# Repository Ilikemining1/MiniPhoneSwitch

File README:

The goal of this project is to build an analog phone switch supporting up to 8 stations and 2 analog trunks.  The switching itself is to be electromechanical in nature, but the control of the switching process and monitoring of lines will be controlled with a microcontroller.  This switch will be designed to be as modular as possible, as with the PCB manufacturing, its common to get multiple boards for your money, making it ideal that many of the boards are identical.

PCB Files are from KiCad, and simulation files are for LTSpice.

Simulation models are property of their respective companies.

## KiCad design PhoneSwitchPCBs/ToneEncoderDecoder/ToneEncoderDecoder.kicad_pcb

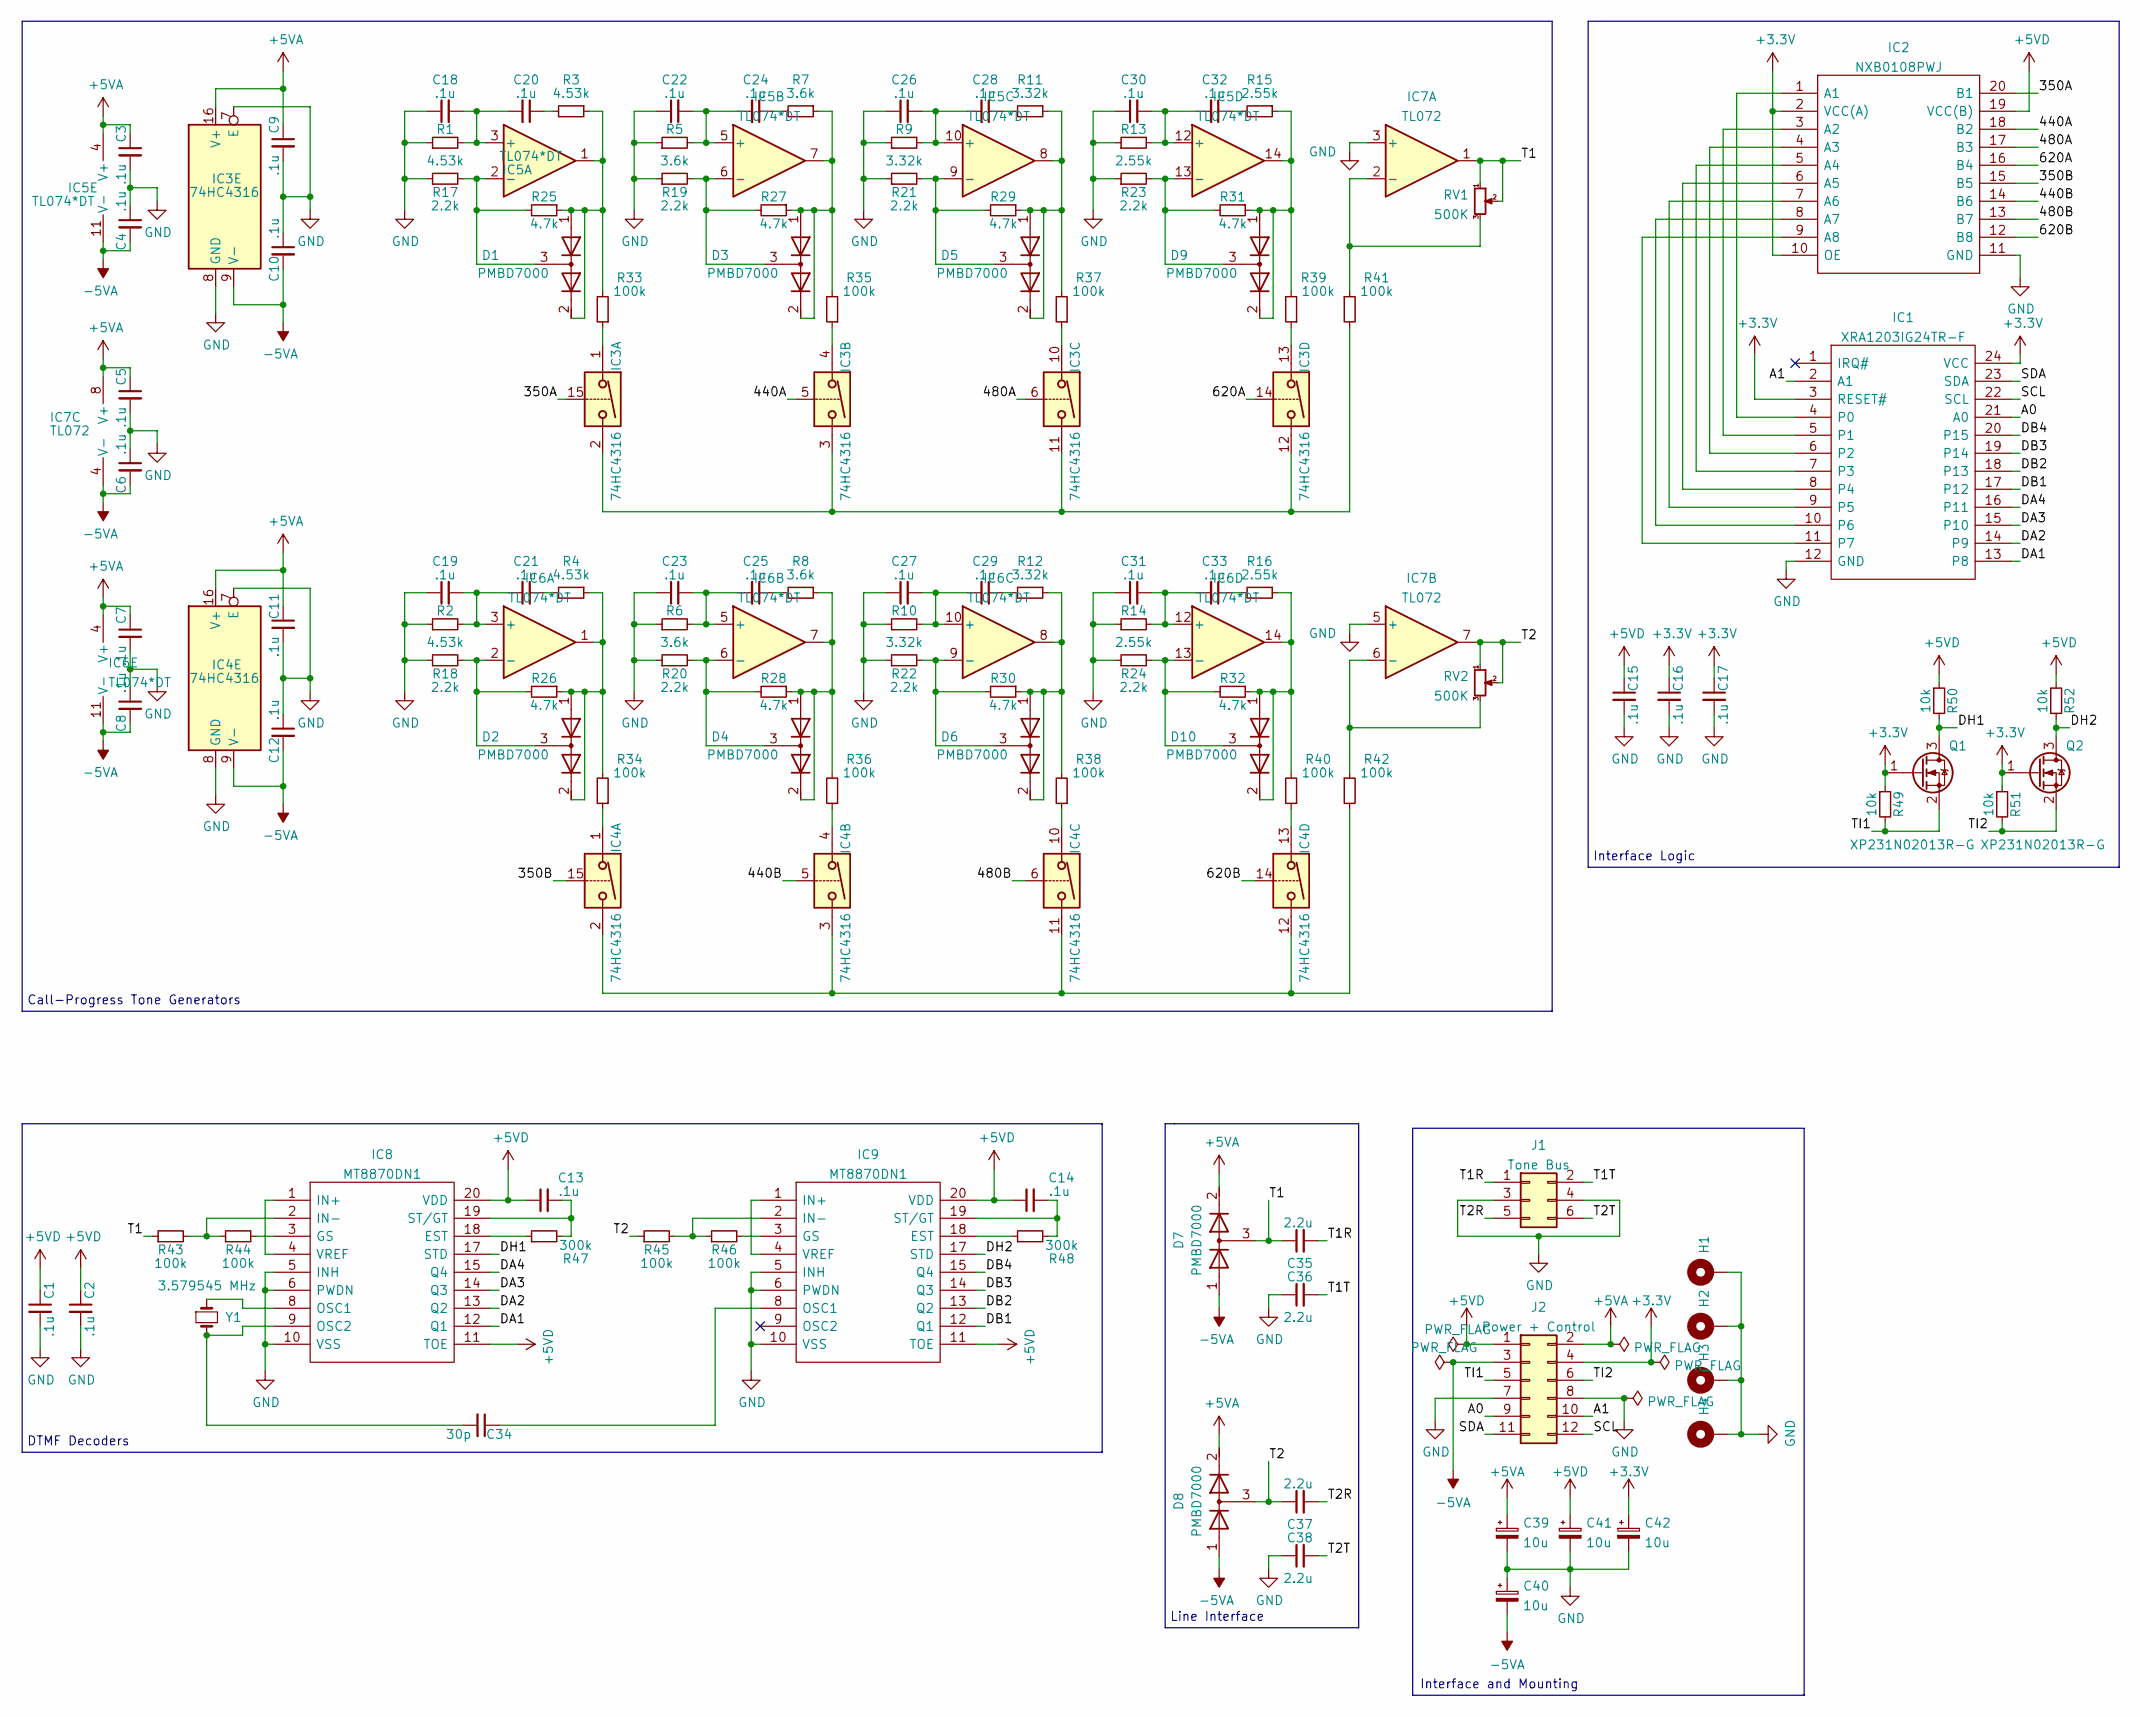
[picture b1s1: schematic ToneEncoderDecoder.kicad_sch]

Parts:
C1, C2, C3, C4, C5, C6, C7, C8, C9, C10, C11, C12, C13, C14, C15, C16, C17: .1u; C_0603_1608Metric_Pad1.08x0.95mm_HandSolder
C18, C19, C20, C21, C22, C23, C24, C25, C26, C27, C28, C29, C30, C31, C32, C33: .1u; C_1206_3216Metric_Pad1.33x1.80mm_HandSolder
C34: 30p; C_0603_1608Metric_Pad1.08x0.95mm_HandSolder
C35, C36, C37, C38: 2.2u; C_Radial_D5.0mm_H11.0mm_P2.00mm
C39, C40, C41, C42: 10u; C_0805_2012Metric_Pad1.18x1.45mm_HandSolder
D1, D2, D3, D4, D5, D6, D7, D8, D9, D10: PMBD7000; SOT-23
H1, H2, H3, H4: M3; MountingHole_3.2mm_M3_Pad
IC1: XRA1203IG24TR-F; TSSOP-24_4.4x7.8mm_P0.65mm
IC2: NXB0108PWJ; TSSOP-20_4.4x6.5mm_P0.65mm
IC3, IC4: 74HC4316; TSSOP-16_4.4x5mm_P0.65mm
IC5, IC6: TL074*DT; SOIC-14_3.9x8.7mm_P1.27mm
IC7: TL072; SOIC-8_3.9x4.9mm_P1.27mm
IC8, IC9: MT8870DN1; SSOP-20_5.3x7.2mm_P0.65mm
J1: Tone Bus; PinHeader_2x03_P2.54mm_Vertical
J2: Power + Control; PinHeader_2x06_P2.54mm_Vertical
Q1, Q2: XP231N02013R-G; SOT-323_SC-70_Handsoldering
R1, R2, R3, R4: 4.53k; R_0603_1608Metric_Pad0.98x0.95mm_HandSolder
R5, R6, R7, R8: 3.6k; R_0603_1608Metric_Pad0.98x0.95mm_HandSolder
R9, R10, R11, R12: 3.32k; R_0603_1608Metric_Pad0.98x0.95mm_HandSolder
R13, R14, R15, R16: 2.55k; R_0603_1608Metric_Pad0.98x0.95mm_HandSolder
R17, R18, R19, R20, R21, R22, R23, R24: 2.2k; R_0603_1608Metric_Pad0.98x0.95mm_HandSolder
R25, R26, R27, R28, R29, R30, R31, R32: 4.7k; R_0603_1608Metric_Pad0.98x0.95mm_HandSolder
R33, R34, R35, R36, R37, R38, R39, R40, R41, R42, R43, R44, R45, R46: 100k; R_0603_1608Metric_Pad0.98x0.95mm_HandSolder
R47, R48: 300k; R_0603_1608Metric_Pad0.98x0.95mm_HandSolder
R49, R50, R51, R52: 10k; R_0603_1608Metric_Pad0.98x0.95mm_HandSolder
RV1, RV2: 500K; Potentiometer_Bourns_3296W_Vertical
Y1: 3.579545 MHz; Crystal_SMD_HC49-SD_HandSoldering

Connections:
+3V3: C16.1, C17.1, C42.1, IC1.3 (RESET#), IC1.24 (VCC), IC2.2 (VCC(A)), IC2.10 (OE), J2.4, Q1.1 (G), Q2.1 (G), R49.1, R51.1
+5VA: C3.1, C5.1, C7.1, C9.1, C11.1, C39.1, D7.2 (K2), D8.2 (K2), IC3.16 (V+), IC4.16 (V+), IC5.4 (V+), IC6.4 (V+), IC7.8 (V+), J2.2
+5VD: C1.1, C2.1, C13.1, C14.1, C15.1, C41.1, IC2.19 (VCC(B)), IC8.11 (TOE), IC8.20 (VDD), IC9.11 (TOE), IC9.20 (VDD), J2.1, R50.1, R52.1
-5VA: C4.2, C6.2, C8.2, C10.2, C12.2, C40.2, D7.1 (A1), D8.1 (A1), IC3.9 (V-), IC4.9 (V-), IC5.11 (V-), IC6.11 (V-), IC7.4 (V-), J2.3
/350A: IC2.20 (B1), IC3.15
/350B: IC2.15 (B5), IC4.15
/440A: IC2.18 (B2), IC3.5
/440B: IC2.14 (B6), IC4.5
/480A: IC2.17 (B3), IC3.6
/480B: IC2.13 (B7), IC4.6
/620A: IC2.16 (B4), IC3.14
/620B: IC2.12 (B8), IC4.14
/A0: IC1.21 (A0), J2.9
/A1: IC1.2 (A1), J2.10
/DA1: IC1.13 (P8), IC8.12 (Q1)
/DA2: IC1.14 (P9), IC8.13 (Q2)
/DA3: IC1.15 (P10), IC8.14 (Q3)
/DA4: IC1.16 (P11), IC8.15 (Q4)
/DB1: IC1.17 (P12), IC9.12 (Q1)
/DB2: IC1.18 (P13), IC9.13 (Q2)
/DB3: IC1.19 (P14), IC9.14 (Q3)
/DB4: IC1.20 (P15), IC9.15 (Q4)
/DH1: IC8.17 (STD), Q1.3 (D), R50.2
/DH2: IC9.17 (STD), Q2.3 (D), R52.2
/SCL: IC1.22 (SCL), J2.12
/SDA: IC1.23 (SDA), J2.11
/T1: C35.1, D7.3 (K1A2), IC7.1, R43.1, RV1.1, RV1.2
/T1R: C35.2, J1.1
/T1T: C36.2, J1.2
/T2: C37.1, D8.3 (K1A2), IC7.7, R45.1, RV2.1, RV2.2
/T2R: C37.2, J1.5
/T2T: C38.2, J1.6
/TI1: J2.5, Q1.2 (S), R49.2
/TI2: J2.6, Q2.2 (S), R51.2
GND: C1.2, C2.2, C3.2, C4.1, C5.2, C6.1, C7.2, C8.1, C9.2, C10.1, C11.2, C12.1, C15.2, C16.2, C17.2, C18.1, C19.1, C22.1, C23.1, C26.1, C27.1, C30.1, C31.1, C36.1, C38.1, C39.2, C40.1, C41.2, C42.2, H1.1, H2.1, H3.1, H4.1, IC1.12 (GND), IC2.11 (GND), IC3.7 (E), IC3.8 (GND), IC4.7 (E), IC4.8 (GND), IC7.3 (+), IC7.5 (+), IC8.5 (INH), IC8.6 (PWDN), IC8.10 (VSS), IC9.5 (INH), IC9.6 (PWDN), IC9.10 (VSS), J1.3, J1.4, J2.7, J2.8, R1.1, R2.1, R5.1, R6.1, R9.1, R10.1, R13.1, R14.1, R17.1, R18.1, R19.1, R20.1, R21.1, R22.1, R23.1, R24.1
unnamed: C13.2, IC8.19 (ST/GT), R47.2
unnamed: C14.2, IC9.19 (ST/GT), R48.2
unnamed: C18.2, C20.2, IC5.3 (+), R1.2
unnamed: C19.2, C21.2, IC6.3 (+), R2.2
unnamed: C20.1, R3.2
unnamed: C21.1, R4.2
unnamed: C22.2, C24.2, IC5.5 (+), R5.2
unnamed: C23.2, C25.2, IC6.5 (+), R6.2
unnamed: C24.1, R7.2
unnamed: C25.1, R8.2
unnamed: C26.2, C28.2, IC5.10 (+), R9.2
unnamed: C27.2, C29.2, IC6.10 (+), R10.2
unnamed: C28.1, R11.2
unnamed: C29.1, R12.2
unnamed: C30.2, C32.2, IC5.12 (+), R13.2
unnamed: C31.2, C33.2, IC6.12 (+), R14.2
unnamed: C32.1, R15.2
unnamed: C33.1, R16.2
unnamed: C34.1, IC9.8 (OSC1)
unnamed: C34.2, IC8.9 (OSC2), Y1.2
unnamed: D1.1 (A1), D1.2 (K2), IC5.1, R3.1, R25.1, R33.2
unnamed: D1.3 (K1A2), IC5.2 (-), R17.2, R25.2
unnamed: D2.1 (A1), D2.2 (K2), IC6.1, R4.1, R26.1, R34.2
unnamed: D2.3 (K1A2), IC6.2 (-), R18.2, R26.2
unnamed: D3.1 (A1), D3.2 (K2), IC5.7, R7.1, R27.1, R35.2
unnamed: D3.3 (K1A2), IC5.6 (-), R19.2, R27.2
unnamed: D4.1 (A1), D4.2 (K2), IC6.7, R8.1, R28.1, R36.2
unnamed: D4.3 (K1A2), IC6.6 (-), R20.2, R28.2
unnamed: D5.1 (A1), D5.2 (K2), IC5.8, R11.1, R29.1, R37.2
unnamed: D5.3 (K1A2), IC5.9 (-), R21.2, R29.2
unnamed: D6.1 (A1), D6.2 (K2), IC6.8, R12.1, R30.1, R38.2
unnamed: D6.3 (K1A2), IC6.9 (-), R22.2, R30.2
unnamed: D9.1 (A1), D9.2 (K2), IC5.14, R15.1, R31.1, R39.2
unnamed: D9.3 (K1A2), IC5.13 (-), R23.2, R31.2
unnamed: D10.1 (A1), D10.2 (K2), IC6.14, R16.1, R32.1, R40.2
unnamed: D10.3 (K1A2), IC6.13 (-), R24.2, R32.2
unnamed: IC1.4 (P0), IC2.1 (A1)
unnamed: IC1.5 (P1), IC2.3 (A2)
unnamed: IC1.6 (P2), IC2.4 (A3)
unnamed: IC1.7 (P3), IC2.5 (A4)
unnamed: IC1.8 (P4), IC2.6 (A5)
unnamed: IC1.9 (P5), IC2.7 (A6)
unnamed: IC1.10 (P6), IC2.8 (A7)
unnamed: IC1.11 (P7), IC2.9 (A8)
unnamed: IC3.1, R33.1
unnamed: IC3.4, R35.1
unnamed: IC3.10, R37.1
unnamed: IC3.2, IC3.3, IC3.11, IC3.12, R41.2
unnamed: IC3.13, R39.1
unnamed: IC4.1, R34.1
unnamed: IC4.4, R36.1
unnamed: IC4.10, R38.1
unnamed: IC4.2, IC4.3, IC4.11, IC4.12, R42.2
unnamed: IC4.13, R40.1
unnamed: IC7.2 (-), R41.1, RV1.3
unnamed: IC7.6 (-), R42.1, RV2.3
unnamed: IC8.1 (IN+), IC8.4 (VREF)
unnamed: IC8.2 (IN-), R43.2, R44.1
unnamed: IC8.3 (GS), R44.2
unnamed: IC8.8 (OSC1), Y1.1
unnamed: IC8.18 (EST), R47.1
unnamed: IC9.1 (IN+), IC9.4 (VREF)
unnamed: IC9.2 (IN-), R45.2, R46.1
unnamed: IC9.3 (GS), R46.2
unnamed: IC9.18 (EST), R48.1

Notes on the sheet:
Line Interface
Interface Logic
DTMF Decoders
Interface and Mounting
Call-Progress Tone Generators

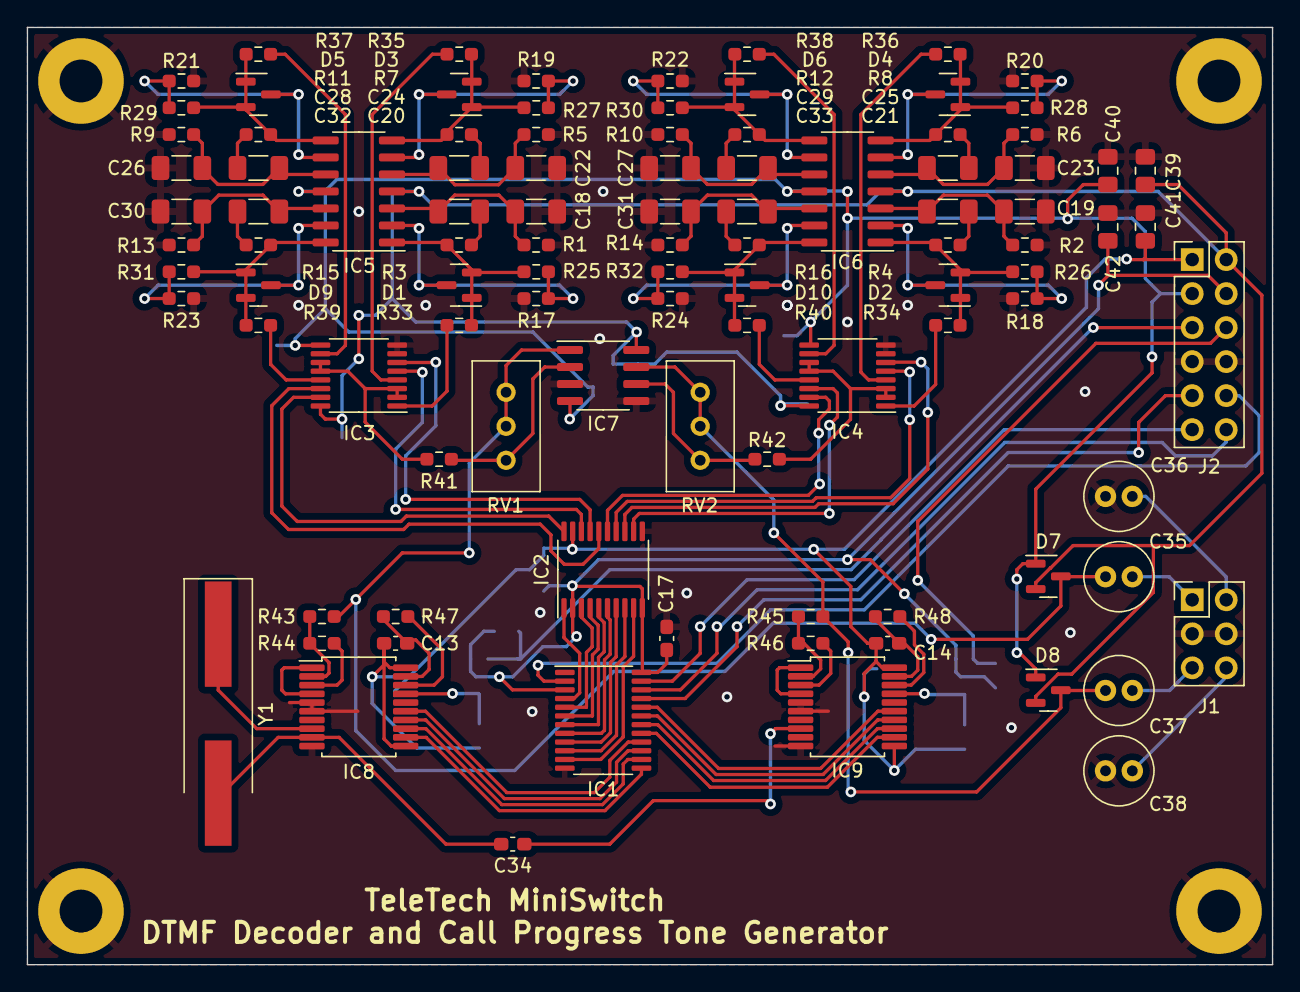
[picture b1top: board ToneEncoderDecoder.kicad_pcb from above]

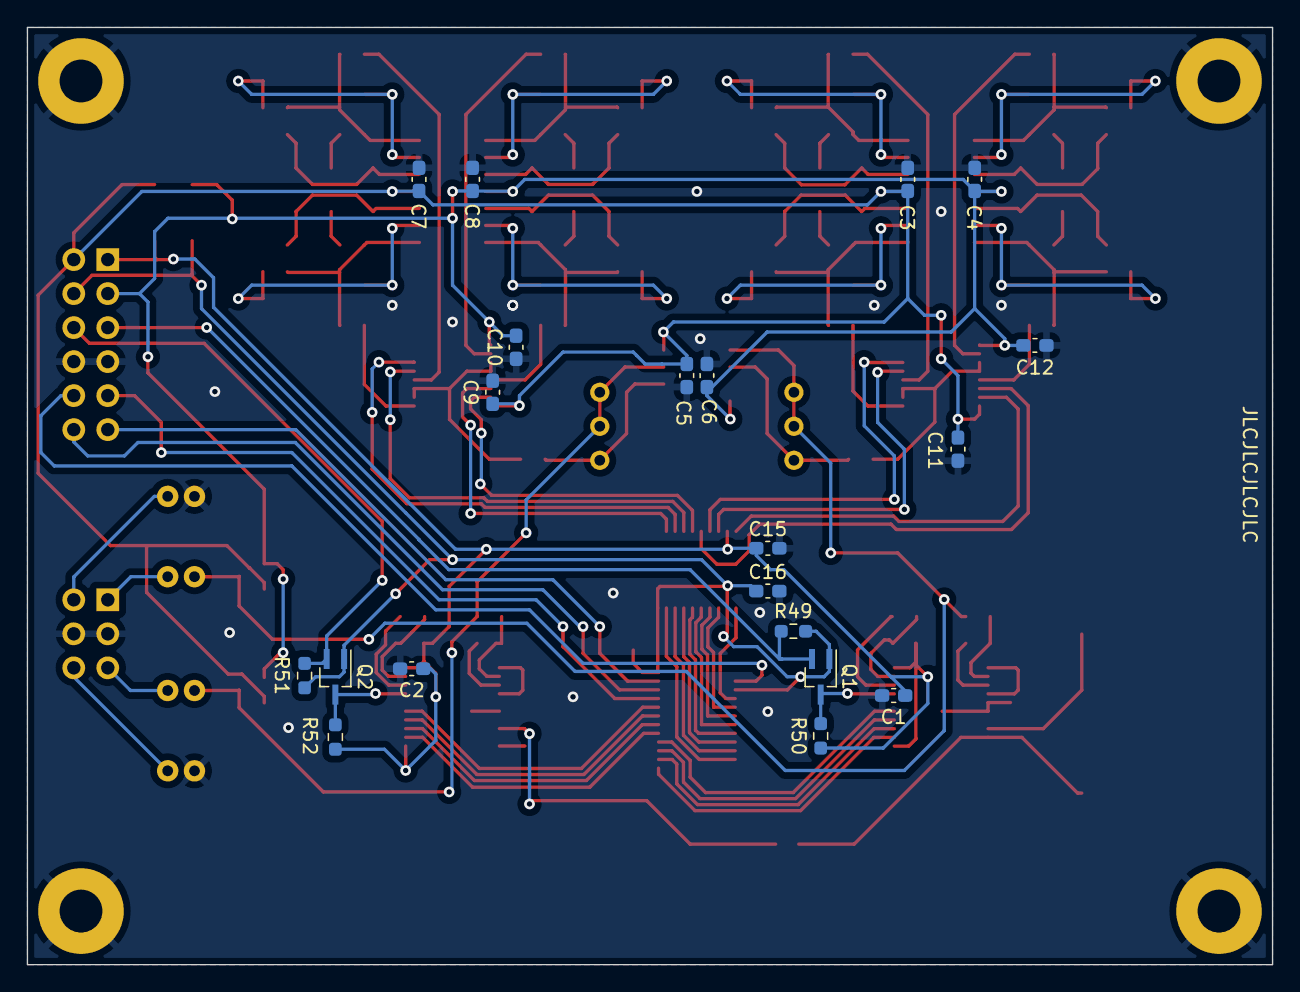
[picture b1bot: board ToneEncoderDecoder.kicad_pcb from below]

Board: 2 copper layers, 93.0 x 70.0 mm, 124 parts (20 on the bottom side), 100 nets.

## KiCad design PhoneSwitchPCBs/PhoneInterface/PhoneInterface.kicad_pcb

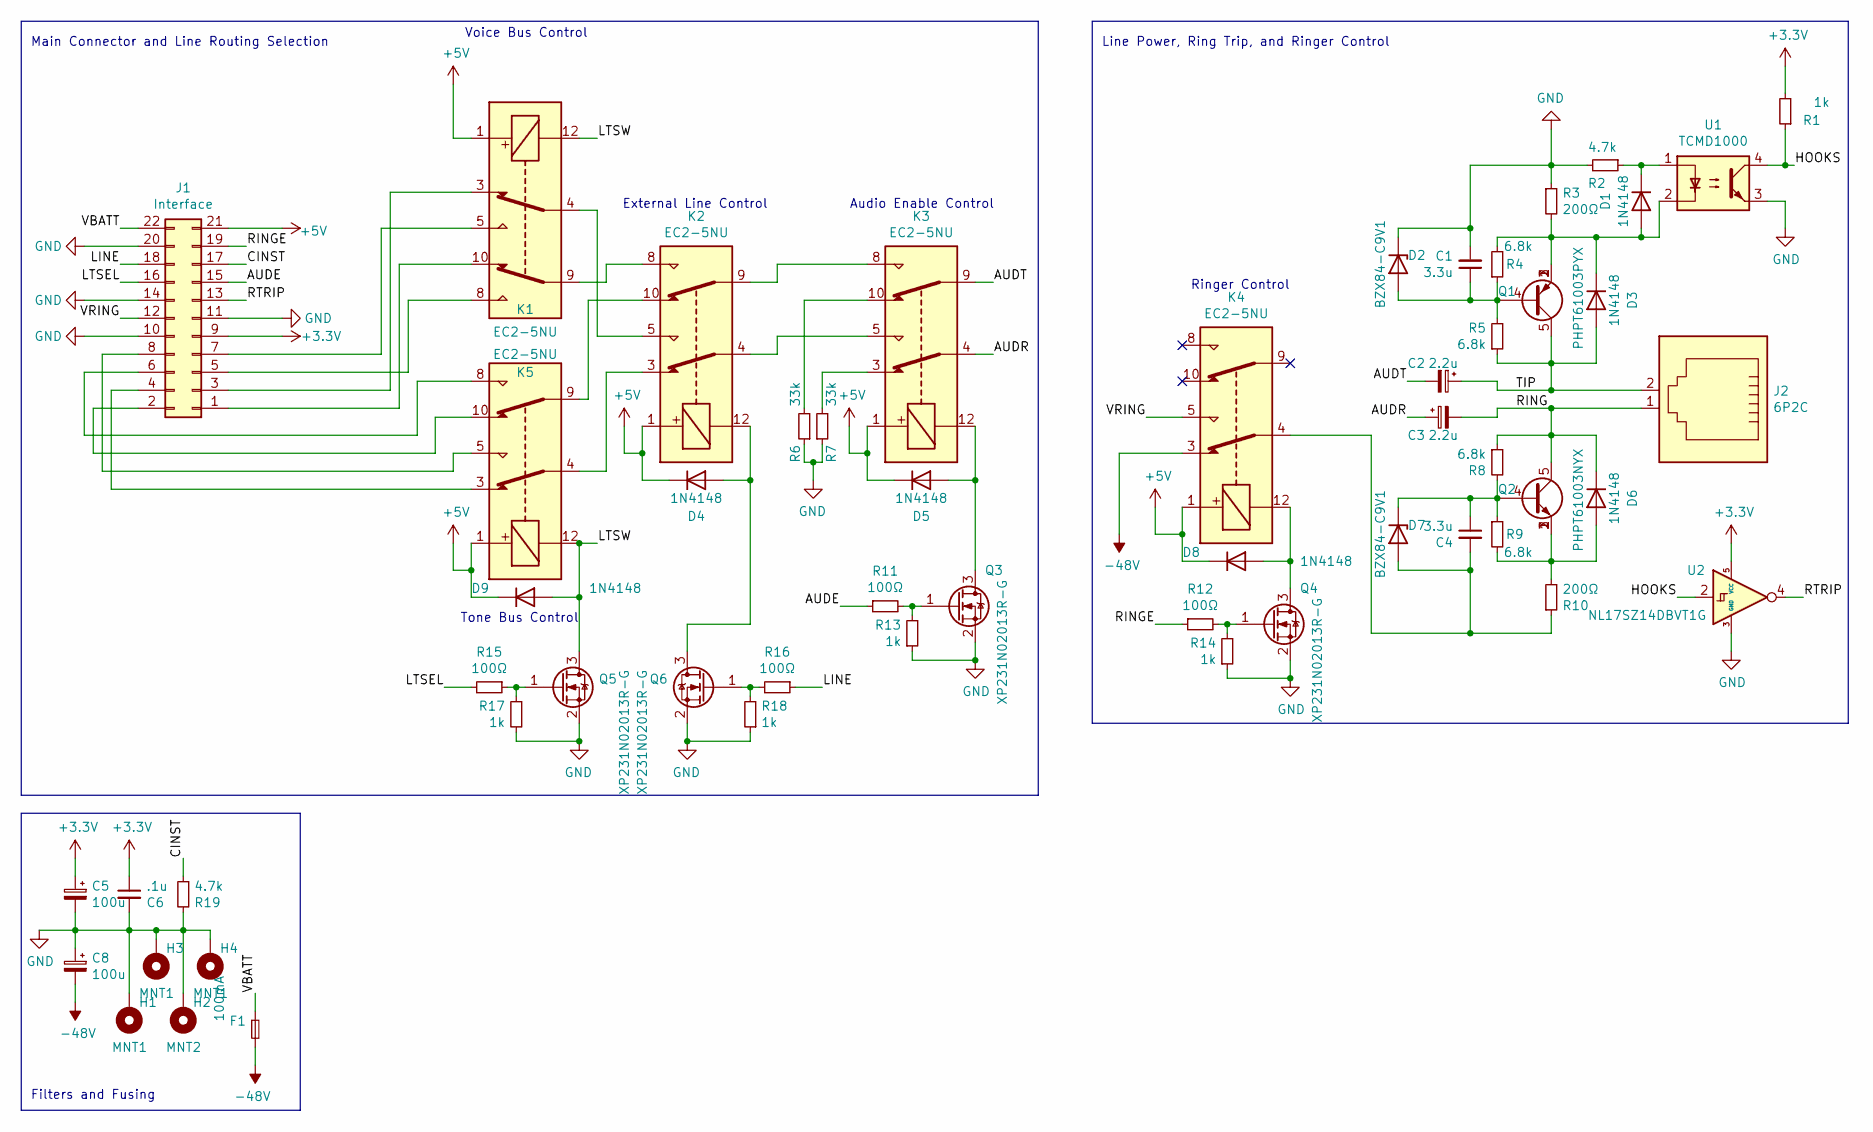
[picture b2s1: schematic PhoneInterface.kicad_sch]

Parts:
C1, C4: 3.3u; CP_Radial_D5.0mm_P2.00mm
C2, C3: 2.2u; CP_Radial_D4.0mm_P1.50mm
C5: 100u; CP_Radial_D5.0mm_P2.00mm
C6: .1u; C_0603_1608Metric_Pad1.08x0.95mm_HandSolder
C8: 100u; CP_Radial_D10.0mm_P5.00mm
D1, D3, D4, D5, D6, D8, D9: 1N4148; D_DO-35_SOD27_P7.62mm_Horizontal
D2, D7: BZX84-C9V1; D_SOT-23_ANK
F1: 100mA; 00346605
H1, H3, H4: MNT1; MountingHole_2.7mm_M2.5_Pad
H2: MNT2; MountingHole_2.7mm_M2.5_Pad
J1: Interface; PinHeader_2x11_P2.54mm_Vertical
J2: 6P2C; RJE0112001
K1, K2, K3, K4, K5: EC2-5NU; Relay_DPDT_Kemet_EC2
Q1: PHPT61003PYX; LFPAK56
Q2: PHPT61003NYX; LFPAK56
Q3, Q4, Q5, Q6: XP231N02013R-G; SOT-323_SC-70_Handsoldering
R1, R13, R14, R17, R18: 1k; R_0805_2012Metric_Pad1.20x1.40mm_HandSolder
R2, R19: 4.7k; R_0805_2012Metric_Pad1.20x1.40mm_HandSolder
R3, R10: 200Ω; R_Axial_DIN0516_L15.5mm_D5.0mm_P20.32mm_Horizontal
R4, R5, R8, R9: 6.8k; R_1210_3225Metric_Pad1.30x2.65mm_HandSolder
R6, R7: 33k; R_0805_2012Metric_Pad1.20x1.40mm_HandSolder
R11, R12, R15, R16: 100Ω; R_0805_2012Metric_Pad1.20x1.40mm_HandSolder
U1: TCMD1000; SOP-4_4.4x2.6mm_P1.27mm
U2: NL17SZ14DBVT1G; SOT-23-5

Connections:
+3V3: C5.1, C6.1, J1.9, R1.2, U2.5 (VCC)
+5V: D4.1 (K), D5.1 (K), D8.1 (K), D9.1 (K), J1.21, K1.1, K2.1, K3.1, K4.1, K5.1; also elsewhere on the board
-48V: C8.2, F1.2, K4.3
/AUDE: J1.15, R11.1
/AUDR: C3.1, K3.4; also elsewhere on the board
/AUDT: C2.2, K3.9; also elsewhere on the board
/CINST: J1.17, R19.1
/HOOKS: R1.1, U1.4, U2.2
/LINE: J1.18, R16.1
/LTSEL: J1.16, R15.2
/LTSW: D9.2 (A), K1.12, K5.12, Q5.3 (D)
/RING: C3.2, D6.1 (K), J2.1, Q2.5 (C), R8.1
/RINGE: J1.19, R12.1
/RTRIP: J1.13, U2.4
/TIP: C2.1, D3.2 (A), J2.2, Q1.5 (C), R5.1
/VBATT: F1.1, J1.22
/VRING: J1.12, K4.5
GND: C1.2, C5.2, C6.2, C8.1, D2.1 (K), H1.1, H2.1, H3.1, H4.1, J1.10, J1.11, J1.14, J1.20, Q3.2 (S), Q4.2 (S), Q5.2 (S), Q6.2 (S), R2.2, R3.1, R6.1, R7.1, R13.1, R14.1, R17.2, R18.1, R19.2, U1.3, U2.3 (GND)
unnamed: C1.1, D2.2 (A), Q1.4 (B), R4.1, R5.2
unnamed: C4.1, D7.1 (K), Q2.4 (B), R8.2, R9.1
unnamed: C4.2, D7.2 (A), K4.4, R10.1
unnamed: D1.1 (K), R2.1, U1.1
unnamed: D1.2 (A), D3.1 (K), Q1.1 (E), Q1.2 (E), Q1.3 (E), R3.2, R4.2, U1.2
unnamed: D4.2 (A), K2.12, Q6.3 (D)
unnamed 24: D5.2 (A), K3.12, Q3.3 (D); also elsewhere on the board
unnamed: D6.2 (A), Q2.1 (E), Q2.2 (E), Q2.3 (E), R9.2, R10.2
unnamed: D8.2 (A), K4.12, Q4.3 (D)
unnamed: J1.1, K1.10
unnamed: J1.2, K5.10
unnamed: J1.3, K1.3
unnamed: J1.4, K5.3
unnamed: J1.5, K1.8
unnamed: J1.6, K5.8
unnamed: J1.7, K1.5
unnamed: J1.8, K5.5
unnamed: K1.4, K2.5
unnamed: K1.9, K2.8
unnamed: K2.3, K5.4
unnamed 38: K2.4, K3.5; also elsewhere on the board
unnamed 39: K2.9, K3.8; also elsewhere on the board
unnamed: K2.10, K5.9
unnamed 41: K3.3, R7.2; also elsewhere on the board
unnamed 42: K3.10, R6.2; also elsewhere on the board
unnamed: Q3.1 (G), R11.2, R13.2
unnamed: Q4.1 (G), R12.2, R14.2
unnamed: Q5.1 (G), R15.1, R17.1
unnamed: Q6.1 (G), R16.2, R18.2

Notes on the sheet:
Ringer Control
Main Connector and Line Routing Selection
External Line Control
Filters and Fusing
Voice Bus Control
Line Power, Ring Trip, and Ringer Control
Tone Bus Control
Audio Enable Control

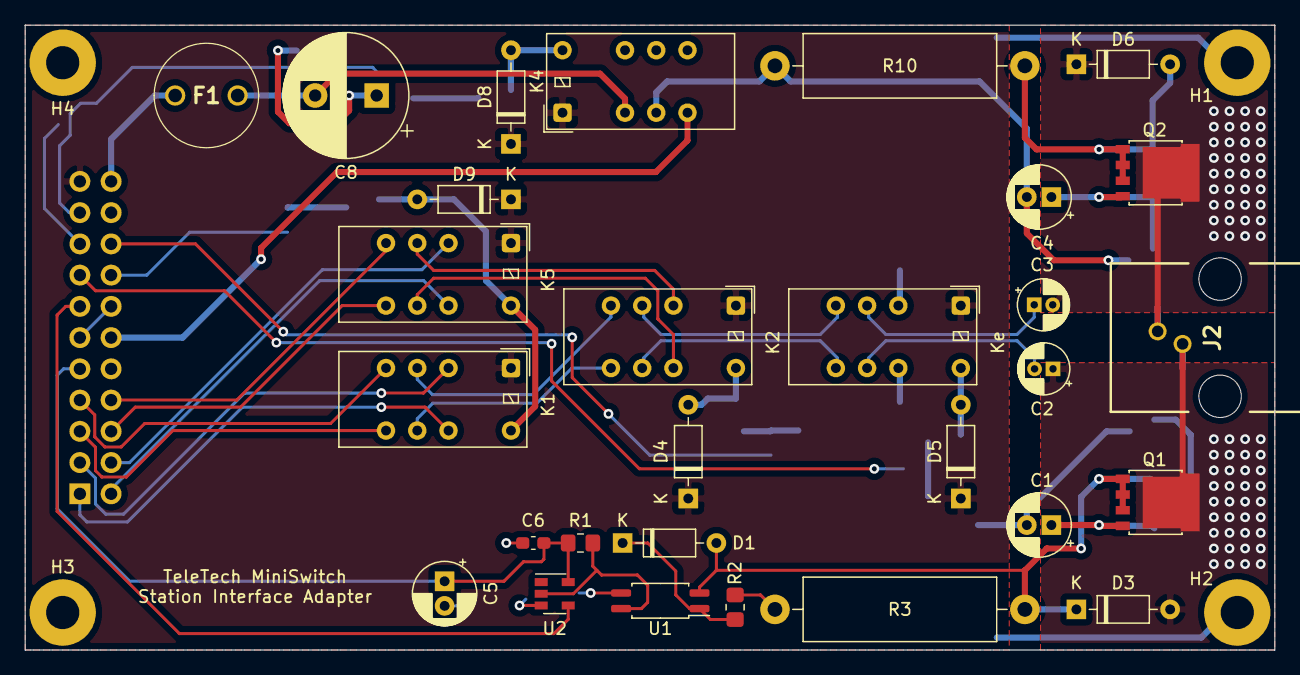
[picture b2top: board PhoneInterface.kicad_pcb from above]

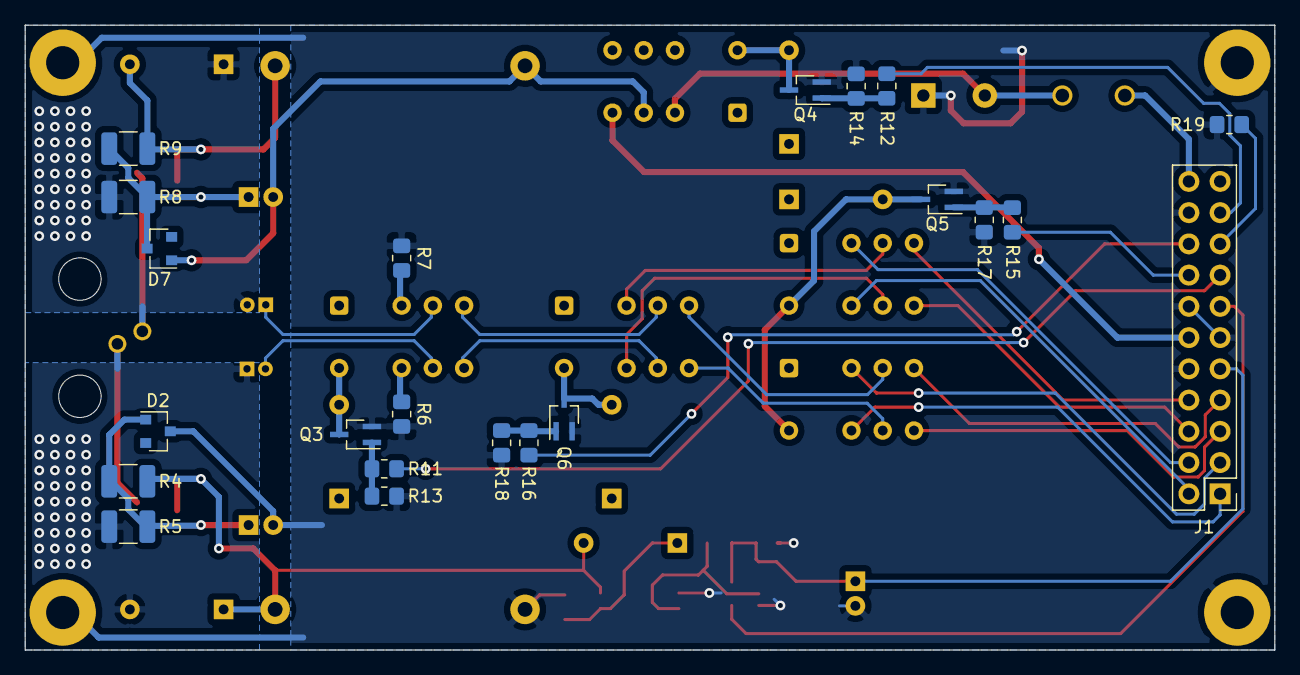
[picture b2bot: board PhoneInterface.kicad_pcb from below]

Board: 2 copper layers, 101.6 x 50.8 mm, 55 parts (22 on the bottom side), 47 nets.

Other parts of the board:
Ke: EC2-5NU; Relay_DPDT_Kemet_EC2

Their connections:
+5V: Ke.1; also elsewhere on the board
/AUDR: Ke.4; also elsewhere on the board
/AUDT: Ke.9; also elsewhere on the board
unnamed 24: Ke.12; also elsewhere on the board
unnamed 38: Ke.5; also elsewhere on the board
unnamed 39: Ke.8; also elsewhere on the board
unnamed 41: Ke.3; also elsewhere on the board
unnamed 42: Ke.10; also elsewhere on the board
